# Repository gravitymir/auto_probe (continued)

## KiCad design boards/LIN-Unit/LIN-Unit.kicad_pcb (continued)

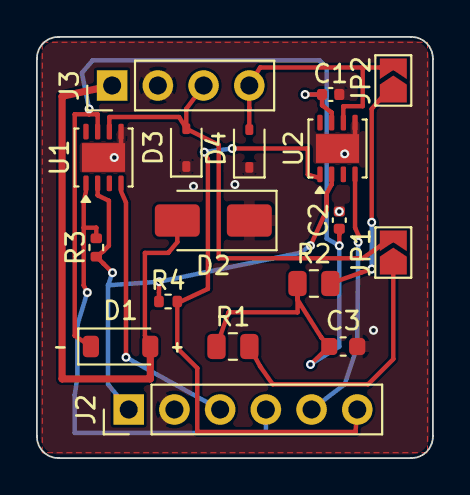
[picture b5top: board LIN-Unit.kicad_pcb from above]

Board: 2 copper layers, 22.0 x 23.4 mm, 17 parts (0 on the bottom side), 12 nets.

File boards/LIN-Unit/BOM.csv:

Comment,Designator,Footprint,LCSC Part #,Qty,Note
100nF,"C1,C2",auto_probe:C_0402_1005Metric,C1525,2,проверить наличие на складе
1uF,C3,auto_probe:C_0603_1608Metric,C15849,1,проверить наличие на складе
SMAJ24CA,D2,auto_probe:D_SMA,C28092,1,проверить наличие на складе
1N4148W,D1,auto_probe:D_SOD-123,C81598,1,проверить наличие на складе
PESD1LIN,"D3,D4",auto_probe:D_SOD-323,C58901,2,проверить наличие на складе
BUS,J3,auto_probe:PinHeader_1x04_P2.54mm_Vertical,,1,"выводная: в SMT-монтаж не идёт, паяется отдельно"
LOGIC,J2,auto_probe:PinHeader_1x06_P2.54mm_Vertical,,1,"выводная: в SMT-монтаж не идёт, паяется отдельно"
10k,"R3,R4",auto_probe:R_0402_1005Metric,C25744,2,проверить наличие на складе
510R,"R1,R2",auto_probe:R_0805_2012Metric,C17734,2,проверить наличие на складе
TLE7258D,"U1,U2",auto_probe:VSON-8-1EP_3x3mm_P0.65mm_EP1.6x2.4mm,C540017,2,проверить наличие на складе

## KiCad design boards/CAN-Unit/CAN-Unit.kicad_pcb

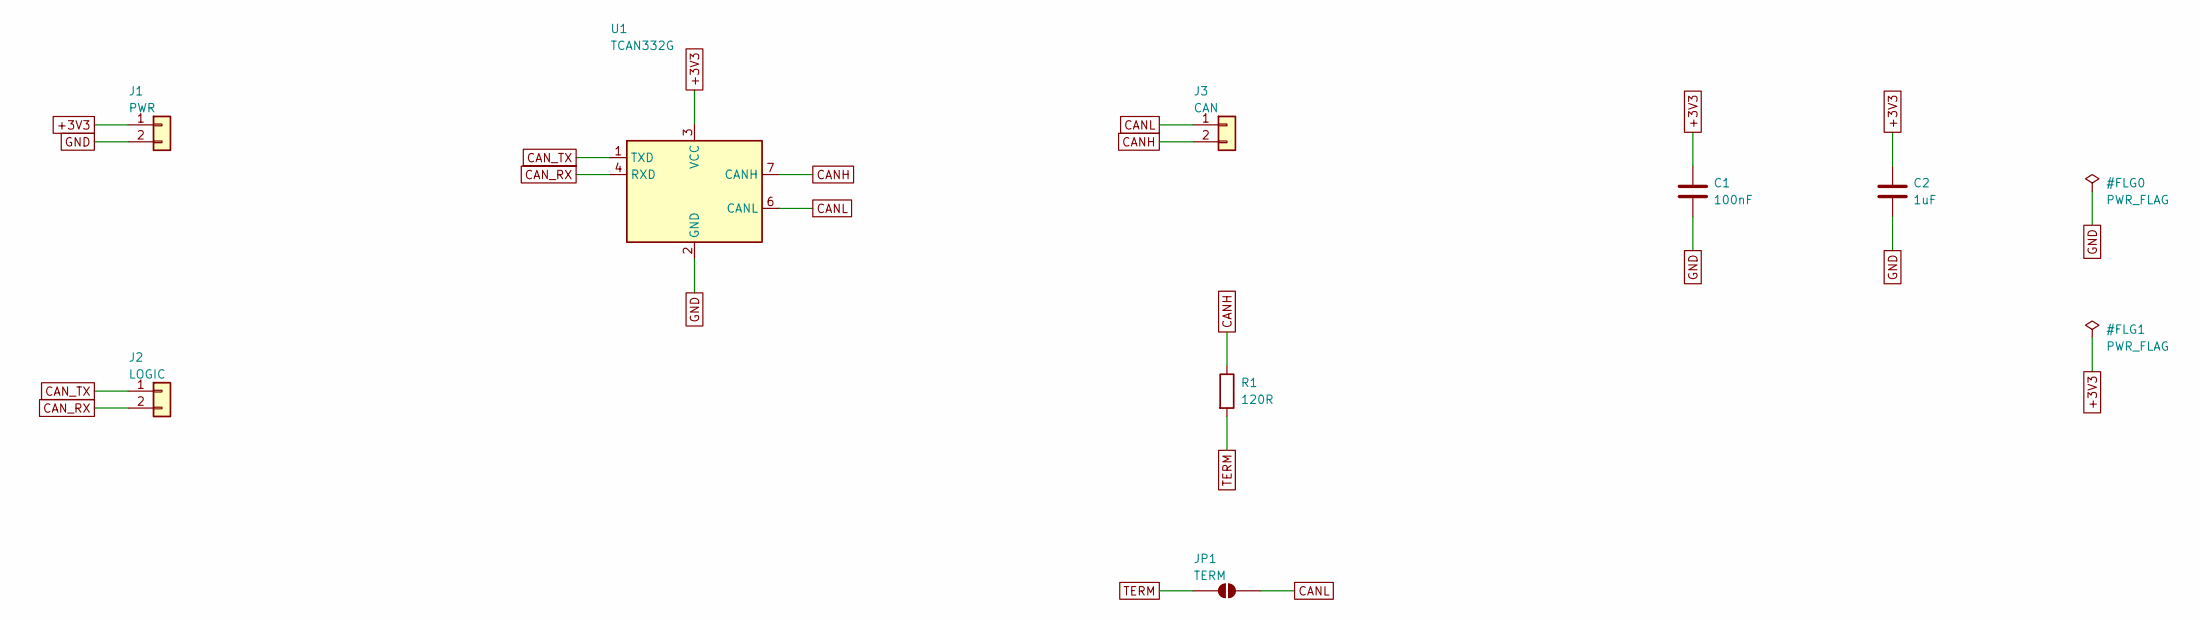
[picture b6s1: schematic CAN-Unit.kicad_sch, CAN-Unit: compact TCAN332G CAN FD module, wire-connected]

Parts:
C1: 100nF; C_0402_1005Metric
C2: 1uF; C_0603_1608Metric
J1: PWR; PinHeader_1x02_P2.54mm_Vertical
J2: LOGIC; PinHeader_1x02_P2.54mm_Vertical
J3: CAN; PinHeader_1x02_P2.54mm_Vertical
JP1: TERM; SolderJumper-2_P1.3mm_Open_TrianglePad1.0x1.5mm
R1: 120R; R_0603_1608Metric
U1: TCAN332G; SOT-23-8

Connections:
+3V3: C1.1, C2.1, J1.1, U1.3 (VCC)
CANH: J3.2, R1.1, U1.7 (CANH)
CANL: J3.1, JP1.2 (B), U1.6 (CANL)
CAN_RX: J2.2, U1.4 (RXD)
CAN_TX: J2.1, U1.1 (TXD)
GND: C1.2, C2.2, J1.2, U1.2 (GND)
TERM: JP1.1 (A), R1.2

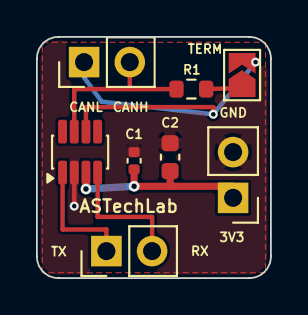
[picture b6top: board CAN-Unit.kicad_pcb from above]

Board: 2 copper layers, 13.0 x 13.4 mm, 8 parts (0 on the bottom side), 7 nets.

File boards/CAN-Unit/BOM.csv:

Comment,Designator,Footprint,LCSC Part #,Qty,Note
100nF,C1,auto_probe:C_0402_1005Metric,C1525,1,проверить наличие на складе
1uF,C2,auto_probe:C_0603_1608Metric,C15849,1,проверить наличие на складе
CAN,J3,auto_probe:PinHeader_1x02_P2.54mm_Vertical,,1,"выводная: в SMT-монтаж не идёт, паяется отдельно"
LOGIC,J2,auto_probe:PinHeader_1x02_P2.54mm_Vertical,,1,"выводная: в SMT-монтаж не идёт, паяется отдельно"
PWR,J1,auto_probe:PinHeader_1x02_P2.54mm_Vertical,,1,"выводная: в SMT-монтаж не идёт, паяется отдельно"
120R,R1,auto_probe:R_0603_1608Metric,C22787,1,проверить наличие на складе
TCAN332G,U1,auto_probe:SOT-23-8,C2671083,1,проверить наличие на складе

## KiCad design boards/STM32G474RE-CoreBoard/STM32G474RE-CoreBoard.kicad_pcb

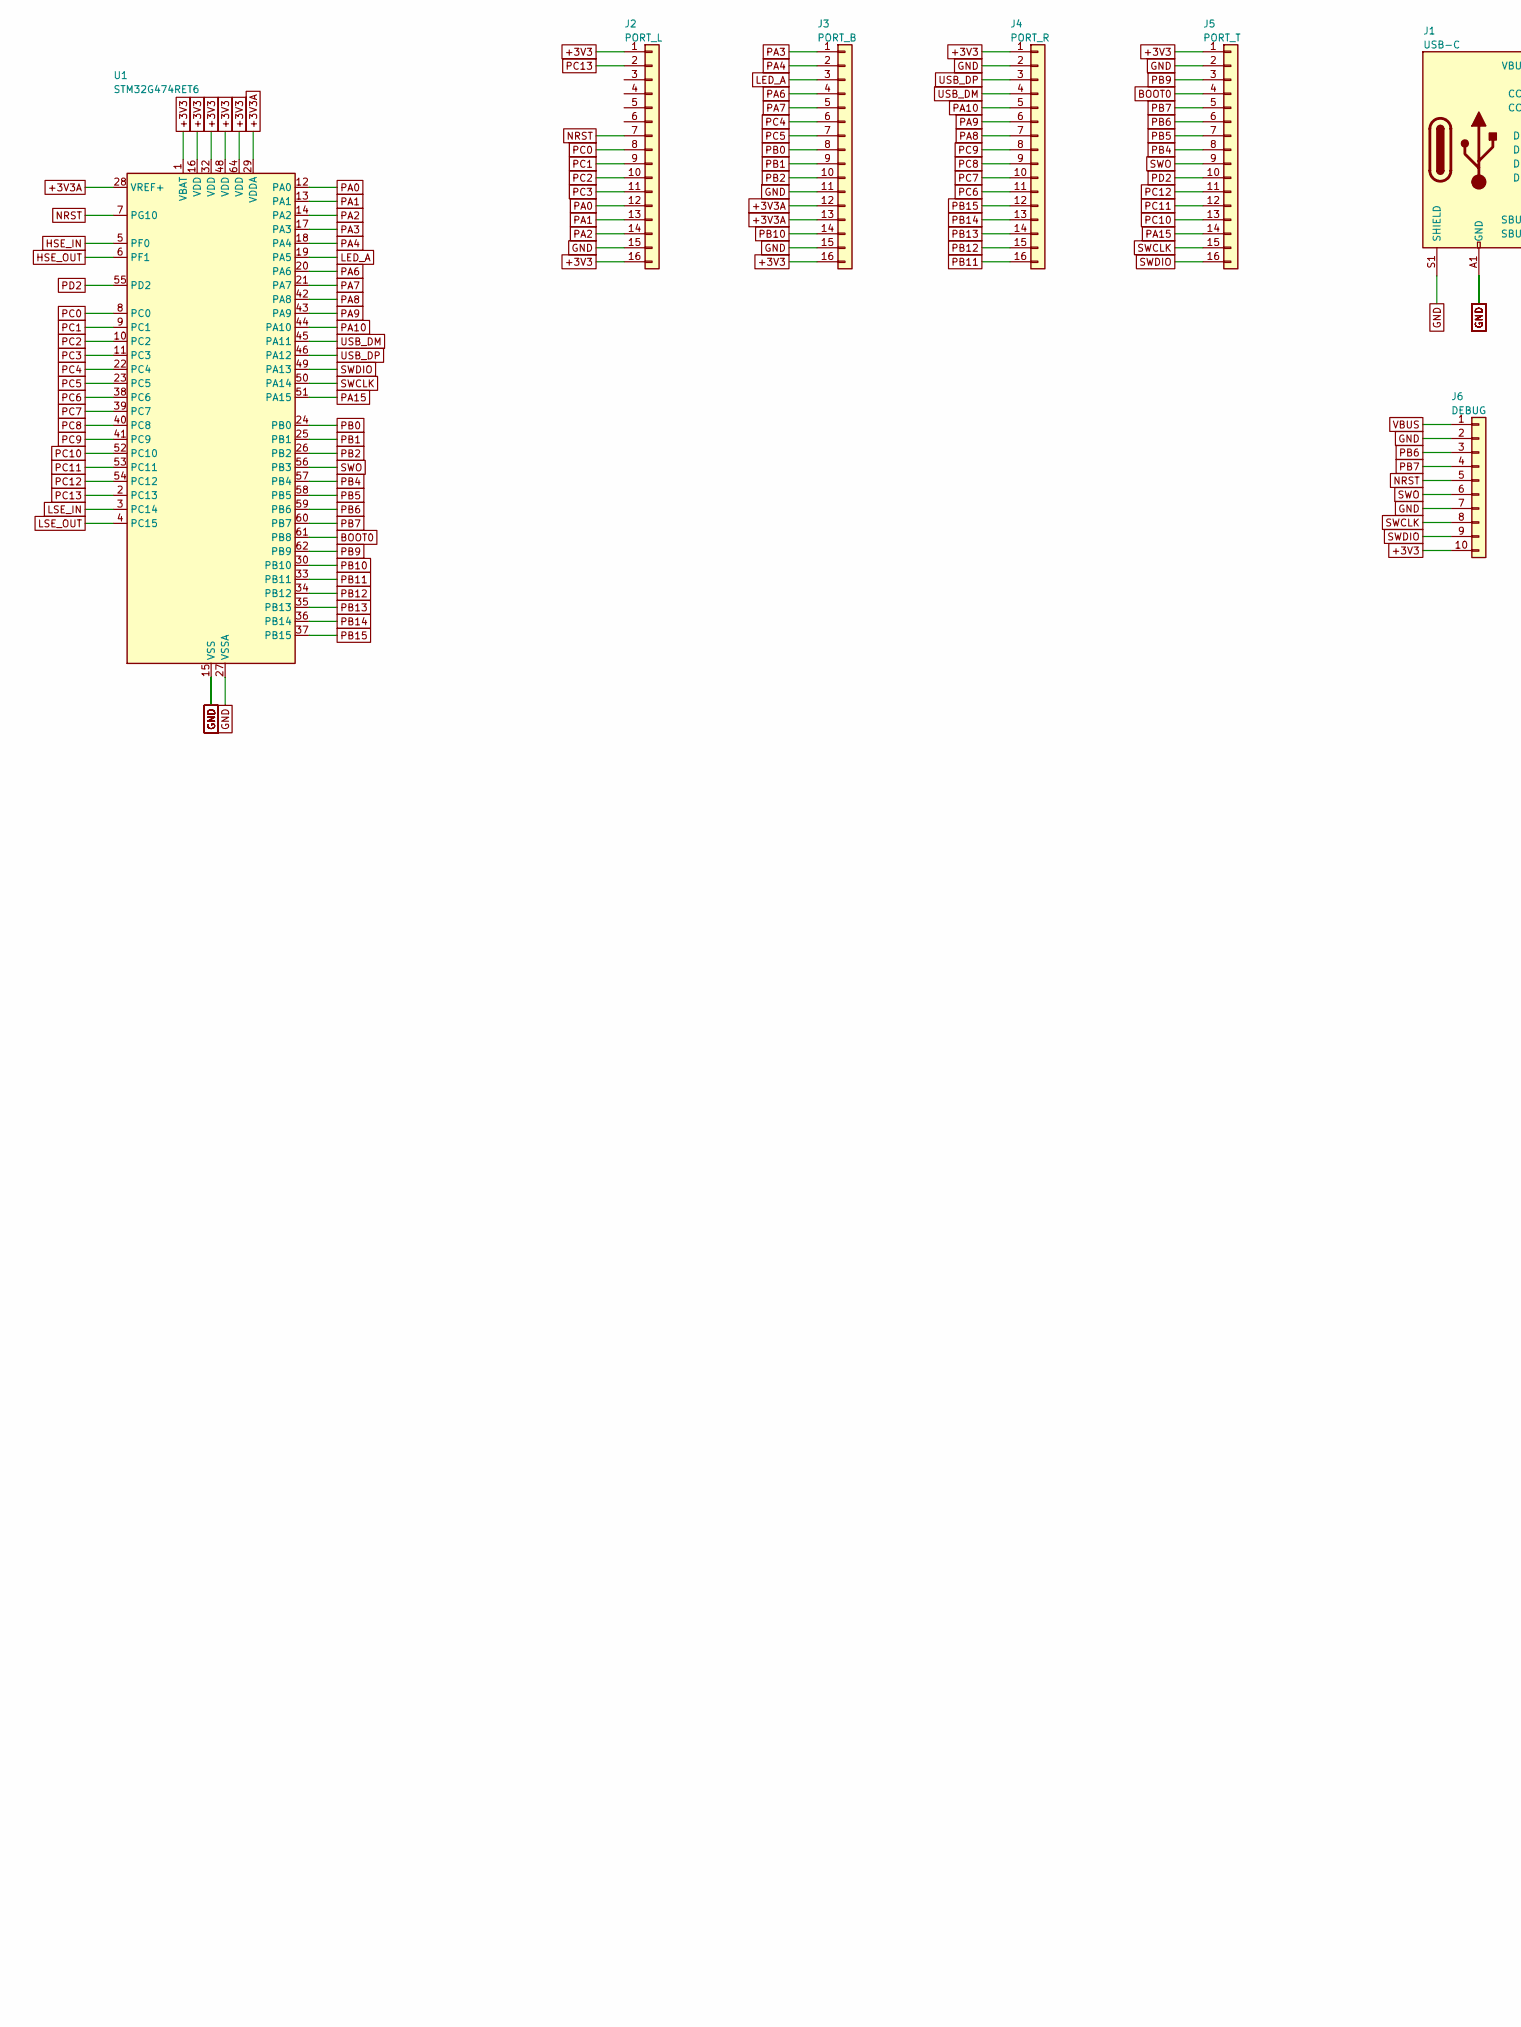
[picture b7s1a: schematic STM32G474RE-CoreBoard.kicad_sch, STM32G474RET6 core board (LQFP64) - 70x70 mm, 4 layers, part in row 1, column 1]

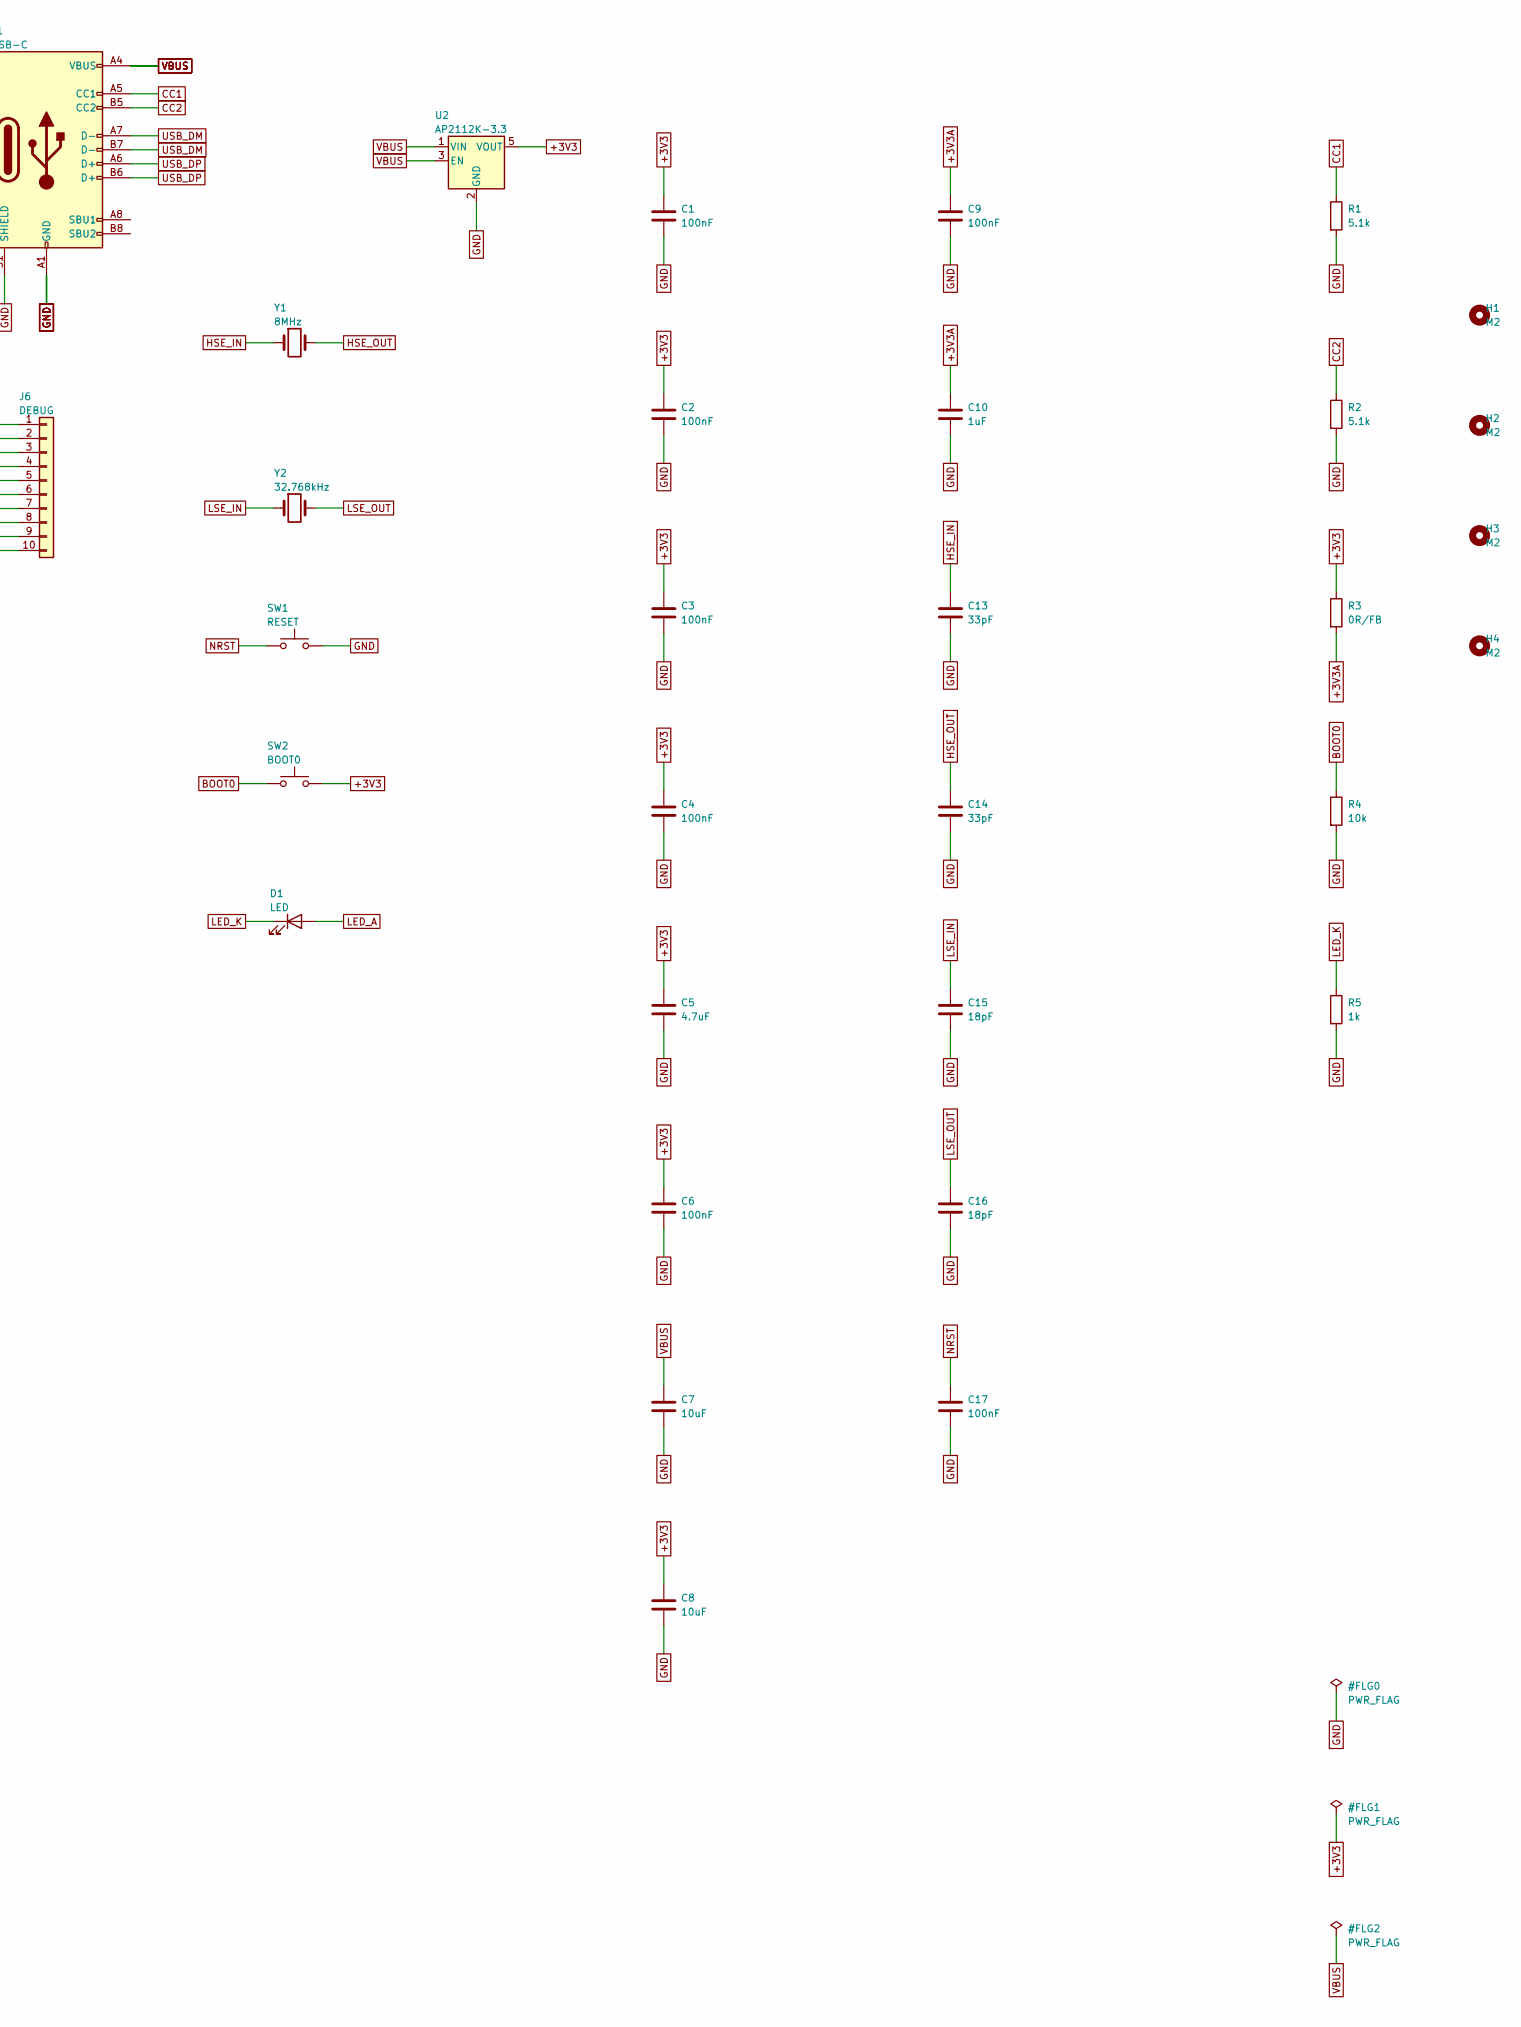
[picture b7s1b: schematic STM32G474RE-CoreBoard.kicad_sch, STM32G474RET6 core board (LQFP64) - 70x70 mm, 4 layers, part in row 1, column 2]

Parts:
C1, C2, C3, C4, C9, C17: 100nF; C_0402_1005Metric
C5: 4.7uF; C_0805_2012Metric
C6: 100nF; C_0603_1608Metric
C7, C8: 10uF; C_0805_2012Metric
C10: 1uF; C_0603_1608Metric
C13, C14: 33pF; C_0402_1005Metric
C15, C16: 18pF; C_0402_1005Metric
D1: LED; LED_0805_2012Metric
H1, H2, H3, H4: M2; MountingHole_2.2mm_M2
J1: USB-C; USB_C_Receptacle_HRO_TYPE-C-31-M-12
J2: PORT_L; PinHeader_1x16_P2.54mm_Vertical
J3: PORT_B; PinHeader_1x16_P2.54mm_Vertical
J4: PORT_R; PinHeader_1x16_P2.54mm_Vertical
J5: PORT_T; PinHeader_1x16_P2.54mm_Vertical
J6: DEBUG; PinHeader_1x10_P2.54mm_Vertical
R1, R2: 5.1k; R_0402_1005Metric
R3: 0R/FB; R_0402_1005Metric
R4: 10k; R_0402_1005Metric
R5: 1k; R_0402_1005Metric
SW1: RESET; SW_SPST_SKQG_WithoutStem
SW2: BOOT0; SW_SPST_SKQG_WithoutStem
U1: STM32G474RET6; LQFP-64_10x10mm_P0.5mm
U2: AP2112K-3.3; SOT-23-5
Y1: 8MHz; Crystal_SMD_5032-2Pin_5.0x3.2mm
Y2: 32.768kHz; Crystal_SMD_MicroCrystal_CC7V-T1A-2Pin_3.2x1.5mm

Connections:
+3V3: C1.1, C2.1, C3.1, C4.1, C5.1, C6.1, C8.1, J2.1, J2.16, J3.16, J4.1, J5.1, J6.10, R3.1, SW2.2, U1.1 (VBAT), U1.16 (VDD), U1.32 (VDD), U1.48 (VDD), U1.64 (VDD), U2.5 (VOUT)
+3V3A: C9.1, C10.1, J3.12, J3.13, R3.2, U1.28 (VREF+), U1.29 (VDDA)
BOOT0: J5.4, R4.1, SW2.1, U1.61 (PB8)
CC1: J1.A5 (CC1), R1.1
CC2: J1.B5 (CC2), R2.1
GND: C1.2, C2.2, C3.2, C4.2, C5.2, C6.2, C7.2, C8.2, C9.2, C10.2, C13.2, C14.2, C15.2, C16.2, C17.2, J1.A1 (GND), J1.A12 (GND), J1.B1 (GND), J1.B12 (GND), J1.S1 (SHIELD), J2.15, J3.11, J3.15, J4.2, J5.2, J6.2, J6.7, R1.2, R2.2, R4.2, R5.2, SW1.2, U1.15 (VSS), U1.27 (VSSA), U1.31 (VSS), U1.47 (VSS), U1.63 (VSS), U2.2 (GND)
HSE_IN: C13.1, U1.5 (PF0), Y1.1
HSE_OUT: C14.1, U1.6 (PF1), Y1.2
LED_A: D1.2 (A), J3.3, U1.19 (PA5)
LED_K: D1.1 (K), R5.1
LSE_IN: C15.1, U1.3 (PC14), Y2.1
LSE_OUT: C16.1, U1.4 (PC15), Y2.2
NRST: C17.1, J2.7, J6.5, SW1.1, U1.7 (PG10)
PA0: J2.12, U1.12 (PA0)
PA1: J2.13, U1.13 (PA1)
PA2: J2.14, U1.14 (PA2)
PA3: J3.1, U1.17 (PA3)
PA4: J3.2, U1.18 (PA4)
PA6: J3.4, U1.20 (PA6)
PA7: J3.5, U1.21 (PA7)
PA8: J4.7, U1.42 (PA8)
PA9: J4.6, U1.43 (PA9)
PA10: J4.5, U1.44 (PA10)
PA15: J5.14, U1.51 (PA15)
PB0: J3.8, U1.24 (PB0)
PB1: J3.9, U1.25 (PB1)
PB2: J3.10, U1.26 (PB2)
PB4: J5.8, U1.57 (PB4)
PB5: J5.7, U1.58 (PB5)
PB6: J5.6, J6.3, U1.59 (PB6)
PB7: J5.5, J6.4, U1.60 (PB7)
PB9: J5.3, U1.62 (PB9)
PB10: J3.14, U1.30 (PB10)
PB11: J4.16, U1.33 (PB11)
PB12: J4.15, U1.34 (PB12)
PB13: J4.14, U1.35 (PB13)
PB14: J4.13, U1.36 (PB14)
PB15: J4.12, U1.37 (PB15)
PC0: J2.8, U1.8 (PC0)
PC1: J2.9, U1.9 (PC1)
PC2: J2.10, U1.10 (PC2)
PC3: J2.11, U1.11 (PC3)
PC4: J3.6, U1.22 (PC4)
PC5: J3.7, U1.23 (PC5)
PC6: J4.11, U1.38 (PC6)
PC7: J4.10, U1.39 (PC7)
PC8: J4.9, U1.40 (PC8)
PC9: J4.8, U1.41 (PC9)
PC10: J5.13, U1.52 (PC10)
PC11: J5.12, U1.53 (PC11)
PC12: J5.11, U1.54 (PC12)
PC13: J2.2, U1.2 (PC13)
PD2: J5.10, U1.55 (PD2)
SWCLK: J5.15, J6.8, U1.50 (PA14)
SWDIO: J5.16, J6.9, U1.49 (PA13)
SWO: J5.9, J6.6, U1.56 (PB3)
USB_DM: J1.A7 (D-), J1.B7 (D-), J4.4, U1.45 (PA11)
USB_DP: J1.A6 (D+), J1.B6 (D+), J4.3, U1.46 (PA12)
VBUS: C7.1, J1.A4 (VBUS), J1.A9 (VBUS), J1.B4 (VBUS), J1.B9 (VBUS), J6.1, U2.1 (VIN), U2.3 (EN)

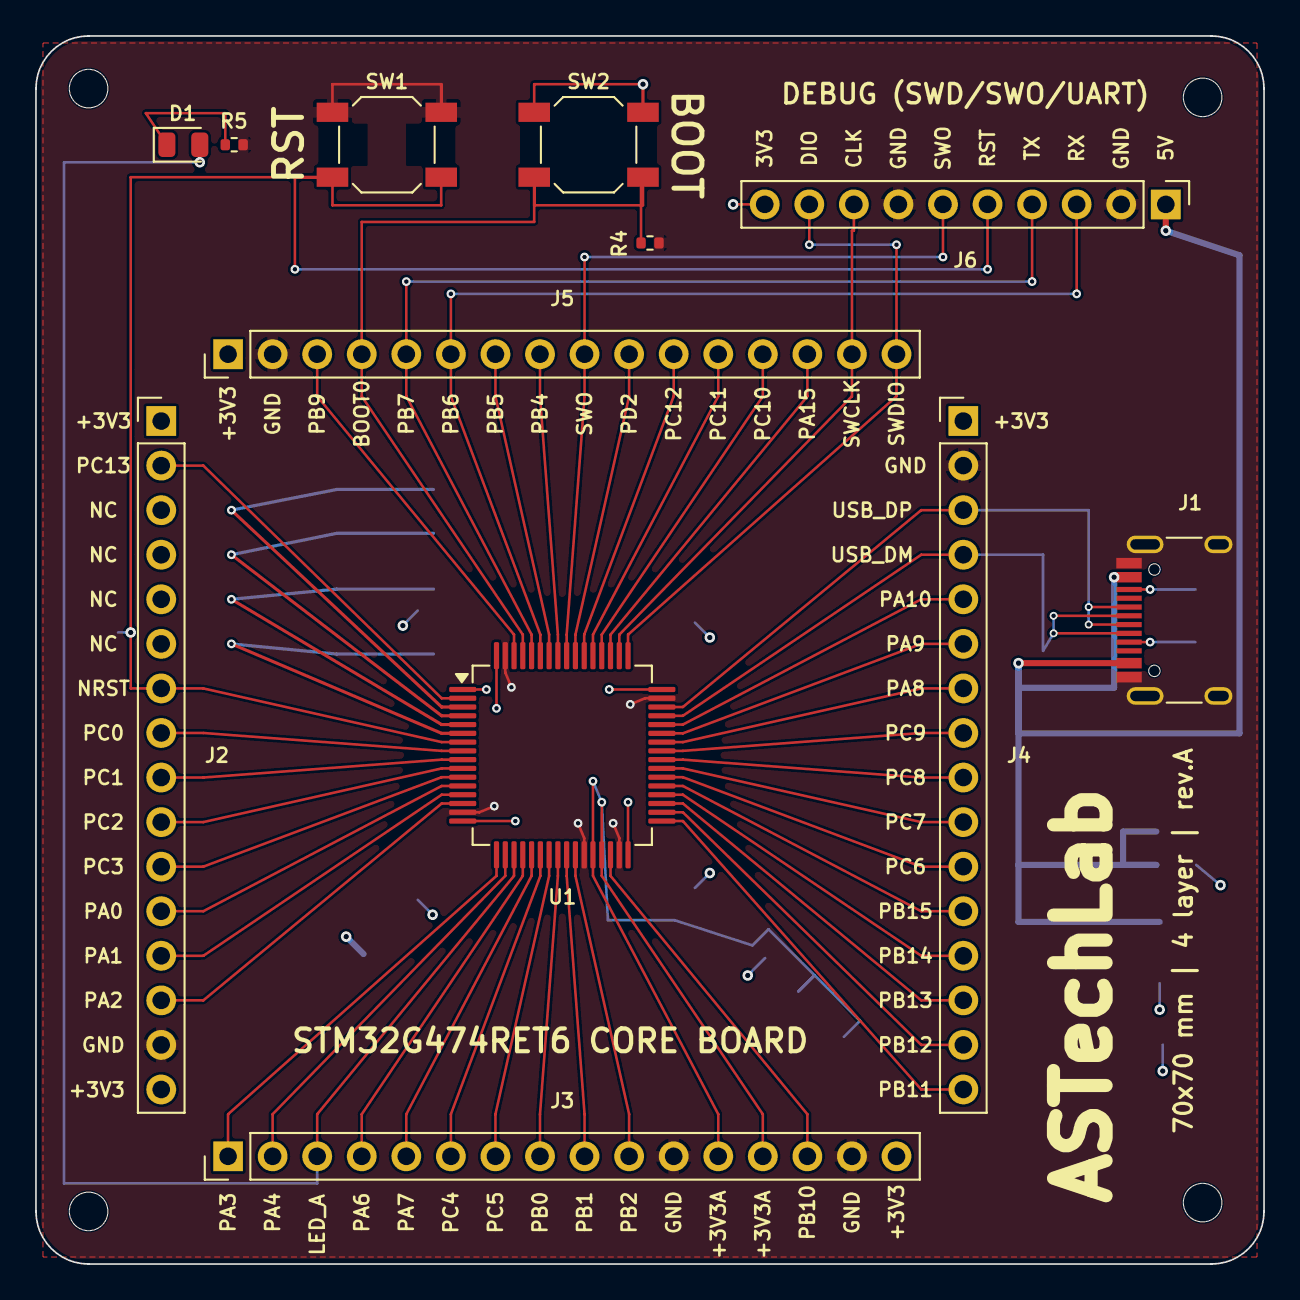
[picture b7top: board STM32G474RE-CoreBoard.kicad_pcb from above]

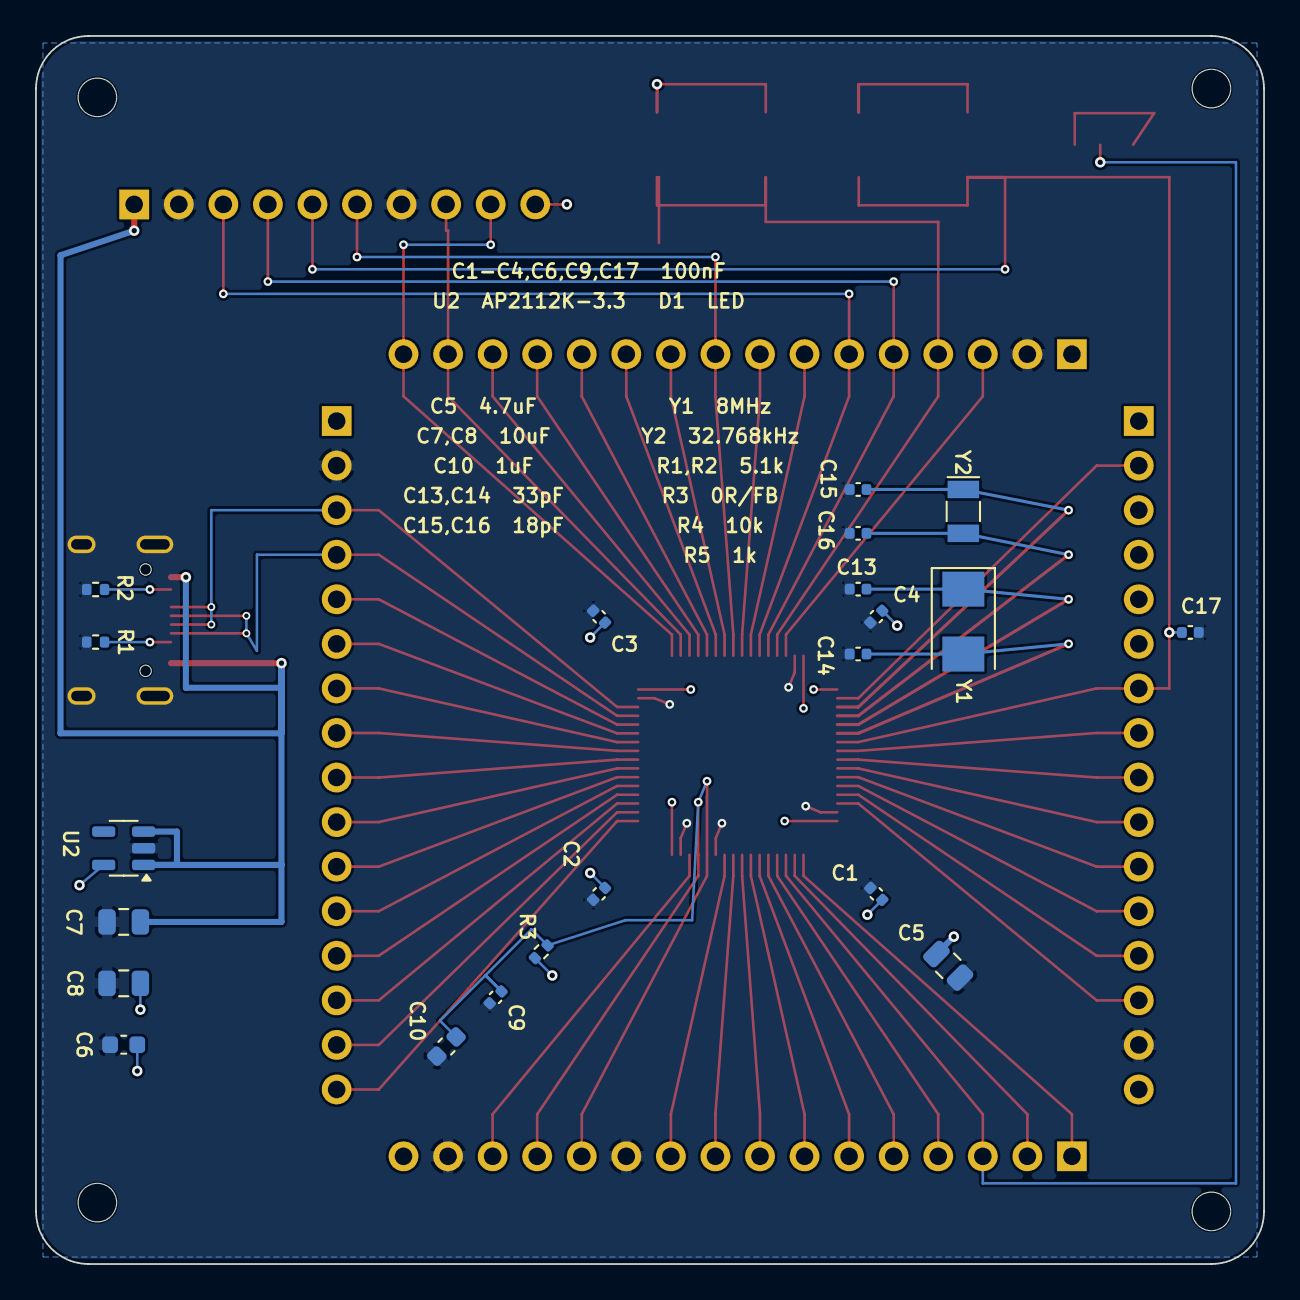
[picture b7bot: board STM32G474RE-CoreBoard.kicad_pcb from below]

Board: 4 copper layers, 70.0 x 70.0 mm, 37 parts (21 on the bottom side), 59 nets.

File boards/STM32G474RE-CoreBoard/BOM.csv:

Comment,Designator,Footprint,LCSC Part #,Qty,Note
100nF,"C1,C17,C2,C3,C4,C9",auto_probe:C_0402_1005Metric,C1525,6,проверить наличие на складе
18pF,"C15,C16",auto_probe:C_0402_1005Metric,C1549,2,проверить наличие на складе
33pF,"C13,C14",auto_probe:C_0402_1005Metric,C1562,2,проверить наличие на складе
100nF,C6,auto_probe:C_0603_1608Metric,C14663,1,проверить наличие на складе
1uF,C10,auto_probe:C_0603_1608Metric,C15849,1,проверить наличие на складе
10uF,"C7,C8",auto_probe:C_0805_2012Metric,C15850,2,проверить наличие на складе
4.7uF,C5,auto_probe:C_0805_2012Metric,C1779,1,проверить наличие на складе
8MHz,Y1,auto_probe:Crystal_SMD_5032-2Pin_5.0x3.2mm,C115962,1,проверить наличие на складе; обвязка 33 пФ - только под CL 20 пФ
32.768kHz,Y2,auto_probe:Crystal_SMD_MicroCrystal_CC7V-T1A-2Pin_3.2x1.5mm,C97606,1,проверить наличие на складе; обвязка 18 пФ - только под CL 12...12.5 пФ
LED,D1,auto_probe:LED_0805_2012Metric,C84256,1,проверить наличие на складе
STM32G474RET6,U1,auto_probe:LQFP-64_10x10mm_P0.5mm,C521608,1,проверить наличие на складе
DEBUG,J6,auto_probe:PinHeader_1x10_P2.54mm_Vertical,,1,"выводная: в SMT-монтаж не идёт, паяется отдельно"
PORT_B,J3,auto_probe:PinHeader_1x16_P2.54mm_Vertical,,1,"выводная: в SMT-монтаж не идёт, паяется отдельно"
PORT_L,J2,auto_probe:PinHeader_1x16_P2.54mm_Vertical,,1,"выводная: в SMT-монтаж не идёт, паяется отдельно"
PORT_R,J4,auto_probe:PinHeader_1x16_P2.54mm_Vertical,,1,"выводная: в SMT-монтаж не идёт, паяется отдельно"
PORT_T,J5,auto_probe:PinHeader_1x16_P2.54mm_Vertical,,1,"выводная: в SMT-монтаж не идёт, паяется отдельно"
1k,R5,auto_probe:R_0402_1005Metric,C11702,1,проверить наличие на складе
0R/FB,R3,auto_probe:R_0402_1005Metric,C17168,1,проверить наличие на складе
10k,R4,auto_probe:R_0402_1005Metric,C25744,1,проверить наличие на складе
5.1k,"R1,R2",auto_probe:R_0402_1005Metric,C25905,2,проверить наличие на складе
AP2112K-3.3,U2,auto_probe:SOT-23-5,C51118,1,"проверить наличие на складе; аналог по выводам ME6211C33M5G-N (C82942), SOT-23-5, 1 VIN / 2 GND / 3 EN / 5 VOUT"
BOOT0/RESET,"SW1,SW2",auto_probe:SW_SPST_SKQG_WithoutStem,C318884,2,проверить наличие на складе
USB-C,J1,auto_probe:USB_C_Receptacle_HRO_TYPE-C-31-M-12,C165948,1,проверить наличие на складе
